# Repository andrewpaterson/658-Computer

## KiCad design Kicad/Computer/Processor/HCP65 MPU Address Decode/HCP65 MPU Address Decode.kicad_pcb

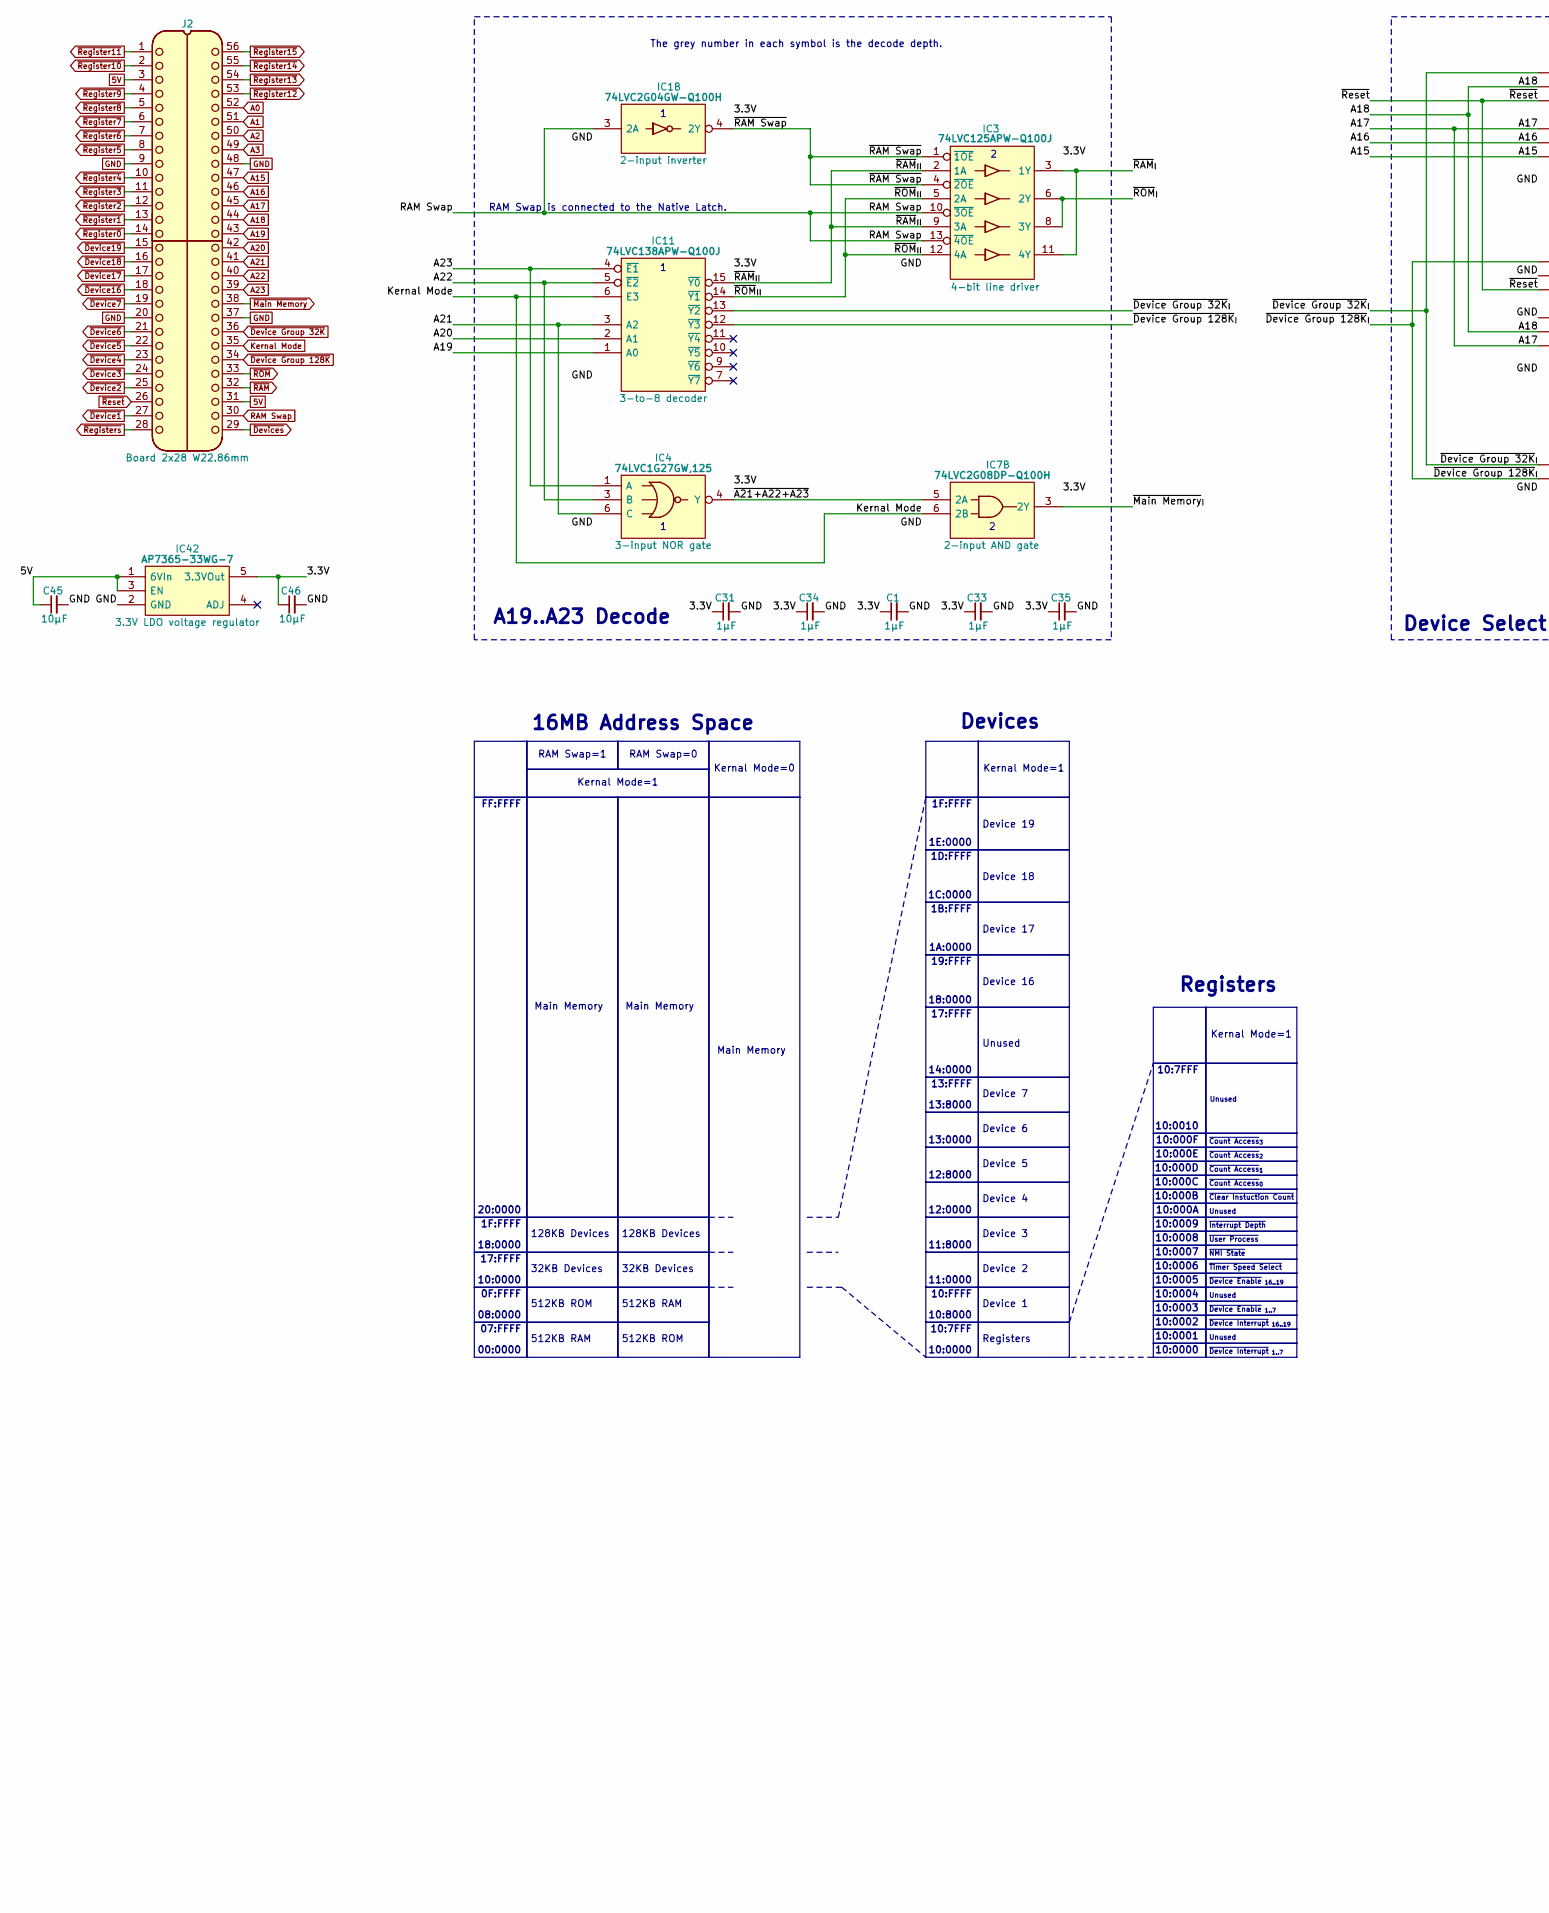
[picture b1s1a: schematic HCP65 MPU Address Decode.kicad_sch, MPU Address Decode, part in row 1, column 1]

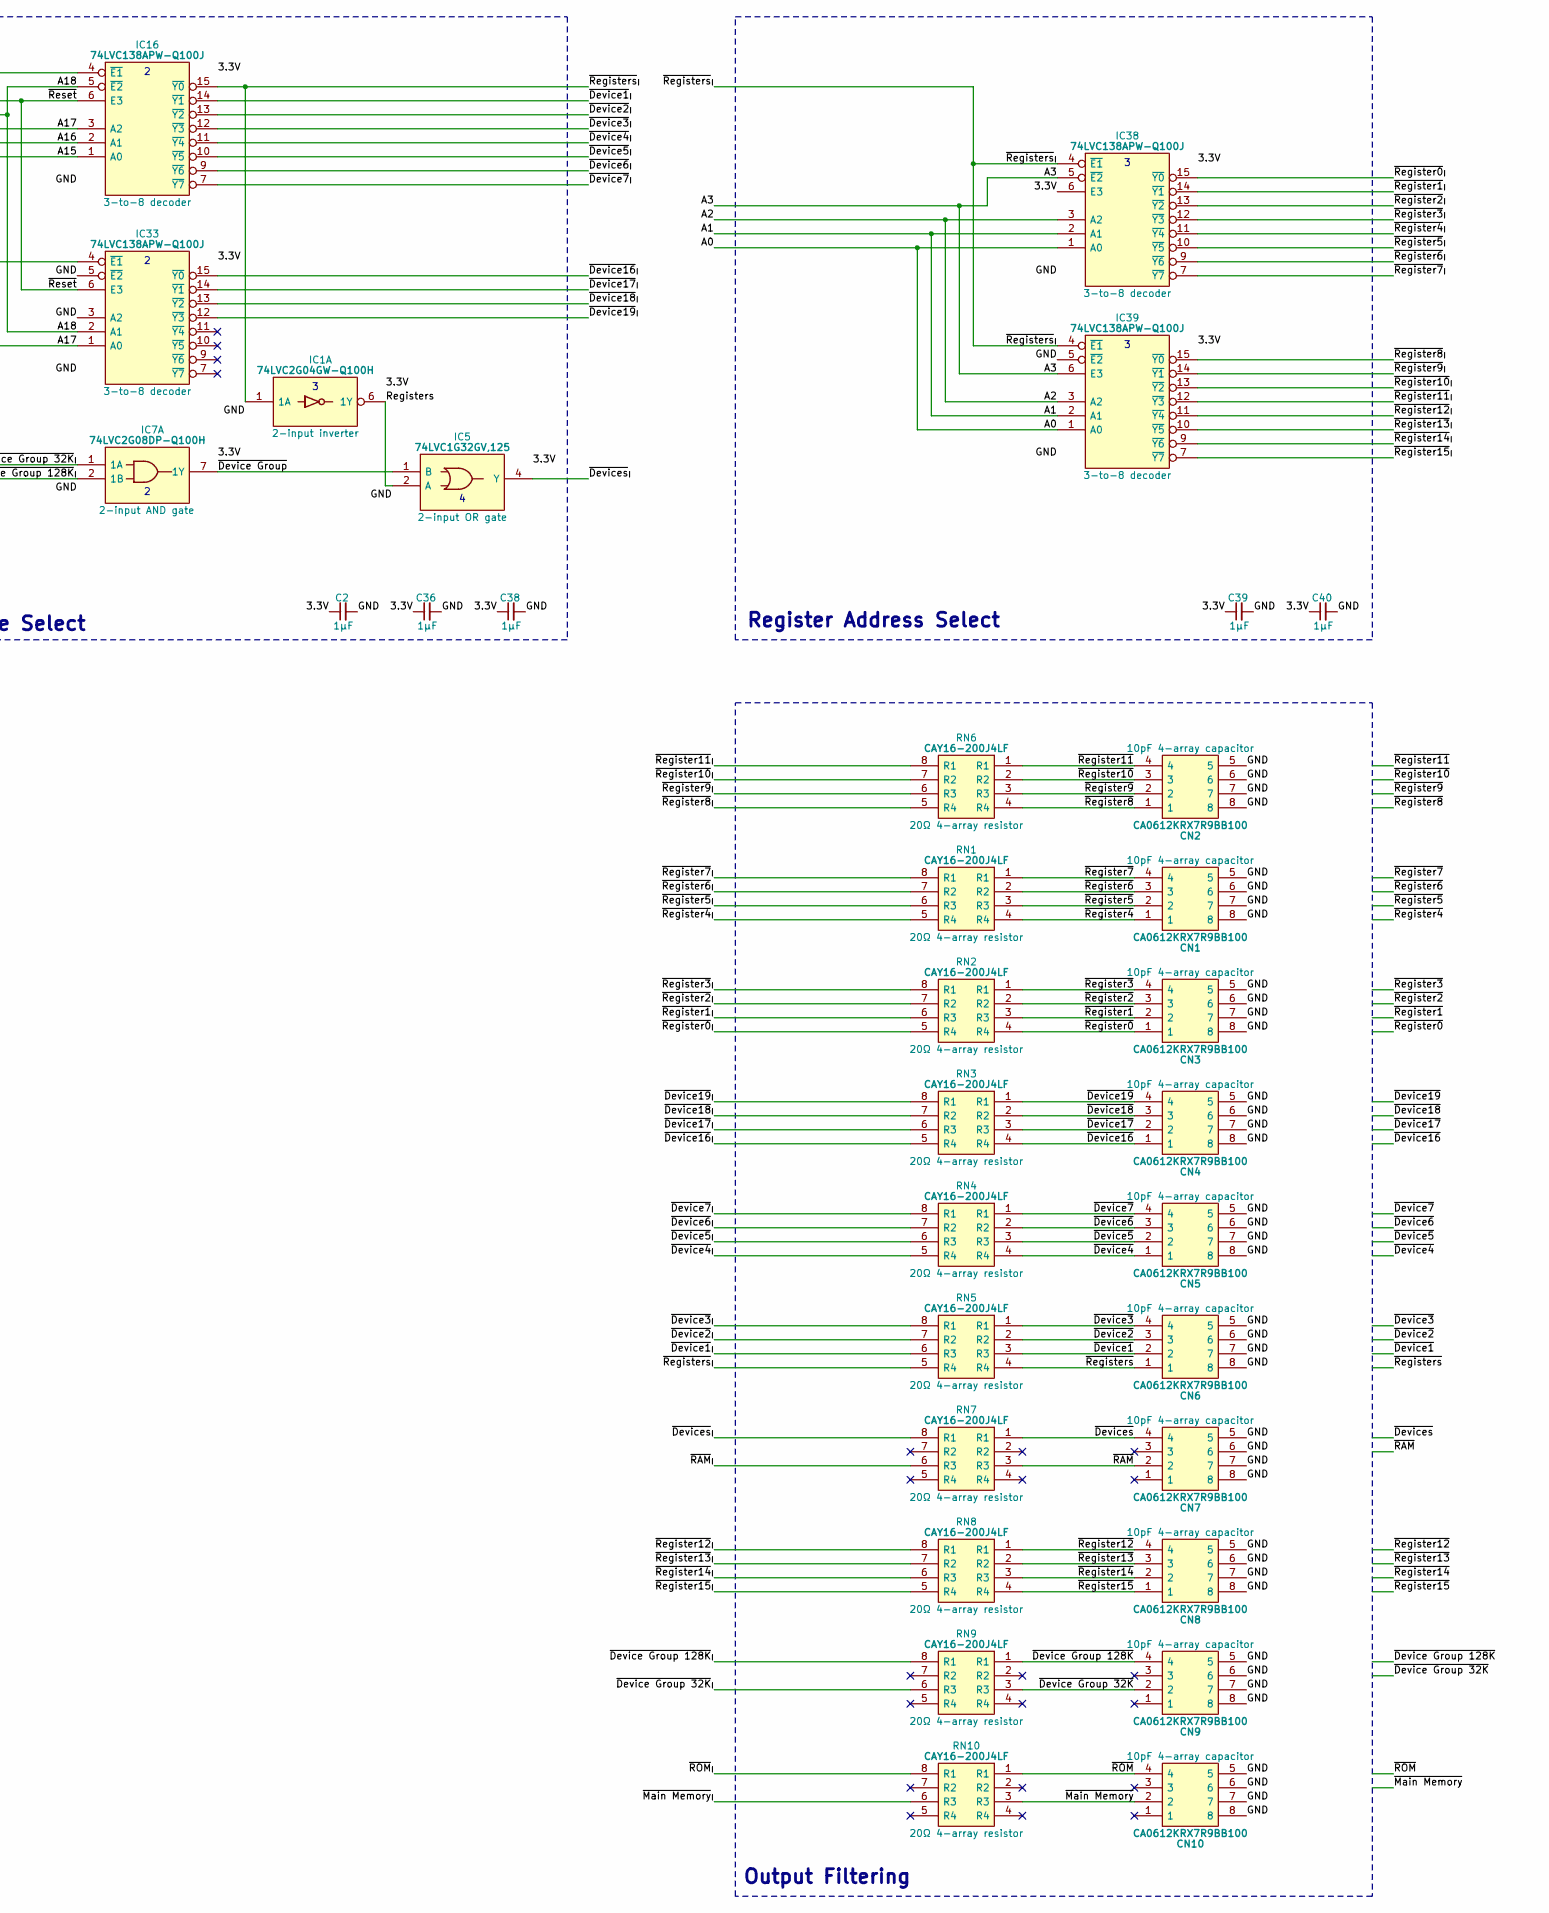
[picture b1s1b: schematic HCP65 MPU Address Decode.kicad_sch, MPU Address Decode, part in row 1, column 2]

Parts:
C1, C2, C31, C33, C34, C35, C36, C38, C39, C40: 1μF; C_0805
C45, C46: 10μF; C_0805
CN1, CN2, CN3, CN4, CN5, CN6, CN7, CN8, CN9, CN10: CA0612KRX7R9BB100; Manufacturer_Part_Number CA0612KRX7R9BB102; Mouser Part Number 603-CA612KRX7R9BB102
IC1: 74LVC2G04GW-Q100H; SOP65P210X110-6N; Manufacturer_Part_Number 74LVC2G04GW-Q100H; Mouser Part Number 771-74LVC2G04GWQ100H
IC3: 74LVC125APW-Q100J; SOP65P640X110-14N; Manufacturer_Part_Number 74LVC125APW-Q100J; Mouser Part Number 771-74LVC125APWQ100J
IC4: 74LVC1G27GW,125; SOP65P210X110-6N; Mouser Part Number 771-74LVC1G27GW125
IC5: 74LVC1G32GV,125; SOT95P275X110-5N; Manufacturer_Part_Number 74LVC1G32GV,125; Mouser Part Number 771-LVC1G32GV125
IC7: 74LVC2G08DP-Q100H; SOP65P400X110-8N; Manufacturer_Part_Number 74LVC2G08DP-Q100H; Mouser Part Number 771-74LVC2G08DPQ100H
IC11, IC16, IC33, IC38, IC39: 74LVC138APW-Q100J; SOP65P640X110-16N; Mouser Part Number 771-74LVC138APWQ100J
IC42: AP7365-33WG-7; SOT95P285X130-5N; Manufacturer_Part_Number AP7365-33WG-7; Mouser Part Number 621-AP7365-33WG-7
J2: Board 2x28 W22.86mm; DIP-56_Board_W22.86mm
RN1, RN2, RN3, RN4, RN5, RN6, RN7, RN8, RN9, RN10: CAY16-200J4LF; CAY16-F4; Manufacturer_Part_Number CAY16-331J4LF; Mouser Part Number 652-CAY16-331J4LF

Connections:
5V: C45.1, IC42.1 (6VIn), IC42.3 (EN), J2.3, J2.31
/3.3V: C1.1, C2.1, C31.1, C33.1, C34.1, C35.1, C36.1, C38.1, C39.1, C40.1, C46.1, IC1.5 (3V), IC3.14 (3V), IC4.5 (3V), IC5.5 (3V), IC7.8 (3V), IC11.16 (3V), IC16.16 (3V), IC33.16 (3V), IC38.6 (E3), IC38.16 (3V), IC39.16 (3V), IC42.5 (3.3VOut)
/Registers: IC1.6 (1Y), IC5.2 (A)
/~A21+A22+A23: IC4.4 (Y), IC7.5 (2A)
/~Device1_{I}: IC16.14 (~Y1), RN5.6 (R3)
/~Device2_{I}: IC16.13 (~Y2), RN5.7 (R2)
/~Device3_{I}: IC16.12 (~Y3), RN5.8 (R1)
/~Device4_{I}: IC16.11 (~Y4), RN4.5 (R4)
/~Device5_{I}: IC16.10 (~Y5), RN4.6 (R3)
/~Device6_{I}: IC16.9 (~Y6), RN4.7 (R2)
/~Device7_{I}: IC16.7 (~Y7), RN4.8 (R1)
/~Device16_{I}: IC33.15 (~Y0), RN3.5 (R4)
/~Device17_{I}: IC33.14 (~Y1), RN3.6 (R3)
/~Device18_{I}: IC33.13 (~Y2), RN3.7 (R2)
/~Device19_{I}: IC33.12 (~Y3), RN3.8 (R1)
/~Device Group 32K_{I}: IC7.1 (1A), IC11.13 (~Y2), IC16.4 (~E1), RN9.6 (R3)
/~Device Group 128K_{I}: IC7.2 (1B), IC11.12 (~Y3), IC33.4 (~E1), RN9.8 (R1)
/~Device Group: IC5.1 (B), IC7.7 (1Y)
/~Devices_{I}: IC5.4 (Y), RN7.8 (R1)
/~Main Memory_{I}: IC7.3 (2Y), RN10.6 (R3)
/~RAM Swap: IC1.4 (2Y), IC3.1 (~1OE), IC3.4 (~2OE)
/~RAM_{II}: IC3.2 (1A), IC3.9 (3A), IC11.15 (~Y0)
/~RAM_{I}: IC3.3 (1Y), IC3.11 (4Y), RN7.6 (R3)
/~ROM_{II}: IC3.5 (2A), IC3.12 (4A), IC11.14 (~Y1)
/~ROM_{I}: IC3.6 (2Y), IC3.8 (3Y), RN10.8 (R1)
/~Register0_{I}: IC38.15 (~Y0), RN2.5 (R4)
/~Register1_{I}: IC38.14 (~Y1), RN2.6 (R3)
/~Register2_{I}: IC38.13 (~Y2), RN2.7 (R2)
/~Register3_{I}: IC38.12 (~Y3), RN2.8 (R1)
/~Register4_{I}: IC38.11 (~Y4), RN1.5 (R4)
/~Register5_{I}: IC38.10 (~Y5), RN1.6 (R3)
/~Register6_{I}: IC38.9 (~Y6), RN1.7 (R2)
/~Register7_{I}: IC38.7 (~Y7), RN1.8 (R1)
/~Register8_{I}: IC39.15 (~Y0), RN6.5 (R4)
/~Register9_{I}: IC39.14 (~Y1), RN6.6 (R3)
/~Register10_{I}: IC39.13 (~Y2), RN6.7 (R2)
/~Register11_{I}: IC39.12 (~Y3), RN6.8 (R1)
/~Register12_{I}: IC39.11 (~Y4), RN8.8 (R1)
/~Register13_{I}: IC39.10 (~Y5), RN8.7 (R2)
/~Register14_{I}: IC39.9 (~Y6), RN8.6 (R3)
/~Register15_{I}: IC39.7 (~Y7), RN8.5 (R4)
/~Registers_{I}: IC1.1 (1A), IC16.15 (~Y0), IC38.4 (~E1), IC39.4 (~E1), RN5.5 (R4)
A0: IC38.1 (A0), IC39.1 (A0), J2.52
A1: IC38.2 (A1), IC39.2 (A1), J2.51
A2: IC38.3 (A2), IC39.3 (A2), J2.50
A3: IC38.5 (~E2), IC39.6 (E3), J2.49
A15: IC16.1 (A0), J2.47
A16: IC16.2 (A1), J2.46
A17: IC16.3 (A2), IC33.1 (A0), J2.45
A18: IC16.5 (~E2), IC33.2 (A1), J2.44
A19: IC11.1 (A0), J2.43
A20: IC11.2 (A1), J2.42
A21: IC4.6 (C), IC11.3 (A2), J2.41
A22: IC4.3 (B), IC11.5 (~E2), J2.40
A23: IC4.1 (A), IC11.4 (~E1), J2.39
GND: C1.2, C2.2, C31.2, C33.2, C34.2, C35.2, C36.2, C38.2, C39.2, C40.2, C45.2, C46.2, CN1.5, CN1.6, CN1.7, CN1.8, CN2.5, CN2.6, CN2.7, CN2.8, CN3.5, CN3.6, CN3.7, CN3.8, CN4.5, CN4.6, CN4.7, CN4.8, CN5.5, CN5.6, CN5.7, CN5.8, CN6.5, CN6.6, CN6.7, CN6.8, CN7.5, CN7.6, CN7.7, CN7.8, CN8.5, CN8.6, CN8.7, CN8.8, CN9.5, CN9.6, CN9.7, CN9.8, CN10.5, CN10.6, CN10.7, CN10.8, IC1.2 (GND), IC3.7 (GND), IC4.2 (GND), IC5.3 (GND), IC7.4 (GND), IC11.8 (GND), IC16.8 (GND), IC33.3 (A2), IC33.5 (~E2), IC33.8 (GND), IC38.8 (GND), IC39.5 (~E2), IC39.8 (GND), IC42.2 (GND), J2.9, J2.20, J2.37, J2.48
Kernal Mode: IC7.6 (2B), IC11.6 (E3), J2.35
RAM Swap: IC1.3 (2A), IC3.10 (~3OE), IC3.13 (~4OE), J2.30
~Device1: CN6.2, J2.27, RN5.3 (R3)
~Device2: CN6.3, J2.25, RN5.2 (R2)
~Device3: CN6.4, J2.24, RN5.1 (R1)
~Device4: CN5.1, J2.23, RN4.4 (R4)
~Device5: CN5.2, J2.22, RN4.3 (R3)
~Device6: CN5.3, J2.21, RN4.2 (R2)
~Device7: CN5.4, J2.19, RN4.1 (R1)
~Device16: CN4.1, J2.18, RN3.4 (R4)
~Device17: CN4.2, J2.17, RN3.3 (R3)
~Device18: CN4.3, J2.16, RN3.2 (R2)
~Device19: CN4.4, J2.15, RN3.1 (R1)
~Device Group 32K: CN9.2, J2.36, RN9.3 (R3)
~Device Group 128K: CN9.4, J2.34, RN9.1 (R1)
~Devices: CN7.4, J2.29, RN7.1 (R1)
~Main Memory: CN10.2, J2.38, RN10.3 (R3)
~RAM: CN7.2, J2.32, RN7.3 (R3)
~ROM: CN10.4, J2.33, RN10.1 (R1)
~Register0: CN3.1, J2.14, RN2.4 (R4)
~Register1: CN3.2, J2.13, RN2.3 (R3)
~Register2: CN3.3, J2.12, RN2.2 (R2)
~Register3: CN3.4, J2.11, RN2.1 (R1)
~Register4: CN1.1, J2.10, RN1.4 (R4)
~Register5: CN1.2, J2.8, RN1.3 (R3)
~Register6: CN1.3, J2.7, RN1.2 (R2)
~Register7: CN1.4, J2.6, RN1.1 (R1)
~Register8: CN2.1, J2.5, RN6.4 (R4)
~Register9: CN2.2, J2.4, RN6.3 (R3)
~Register10: CN2.3, J2.2, RN6.2 (R2)
~Register11: CN2.4, J2.1, RN6.1 (R1)
~Register12: CN8.4, J2.53, RN8.1 (R1)
~Register13: CN8.3, J2.54, RN8.2 (R2)
~Register14: CN8.2, J2.55, RN8.3 (R3)
~Register15: CN8.1, J2.56, RN8.4 (R4)
~Registers: CN6.1, J2.28, RN5.4 (R4)
~Reset: IC16.6 (E3), IC33.6 (E3), J2.26

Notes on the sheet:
17:FFFF
10:0009
Unused
512KB RAM
18:0000
RAM Swap=1
14:0000
10:0006
13:0000
1E:0000
Main Memory
~{Timer Speed Select}
10:8000
10:000F
Kernal Mode=1
Device 17
Kernal Mode=0
~{Interrupt Depth}
~{Device Enable}_{ 1..7}
1C:0000
10:0001
00:0000
19:FFFF
13:FFFF
~{Device Enable}_{ 16..19}
10:0004
10:0000
10:7FFF
10:FFFF
10:000A
~{Device Interrupt}_{ 16..19}
20:0000
11:0000
~{User Process}
Device 5
128KB Devices
512KB ROM
1B:FFFF
Device 6
Registers

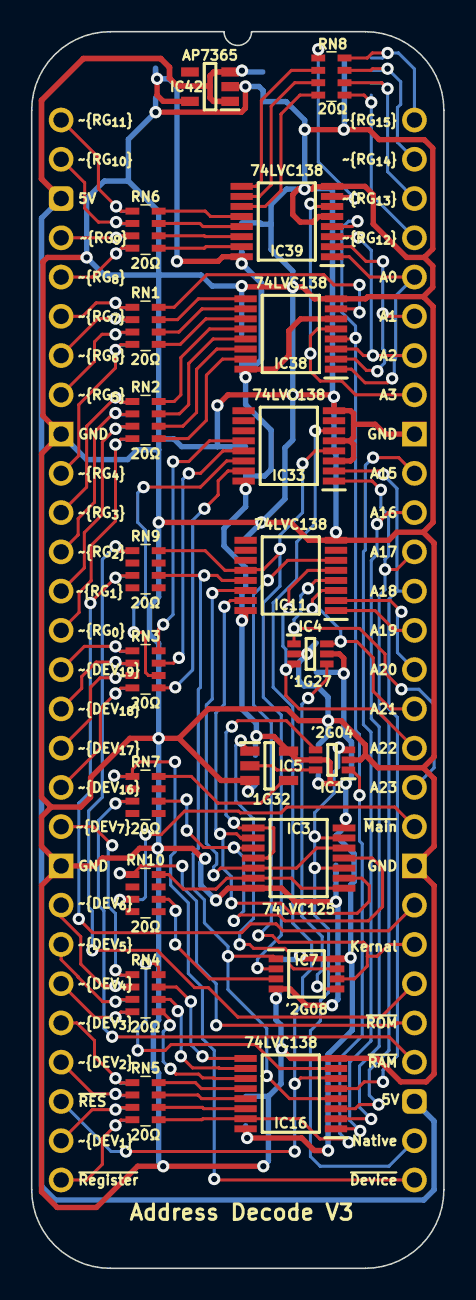
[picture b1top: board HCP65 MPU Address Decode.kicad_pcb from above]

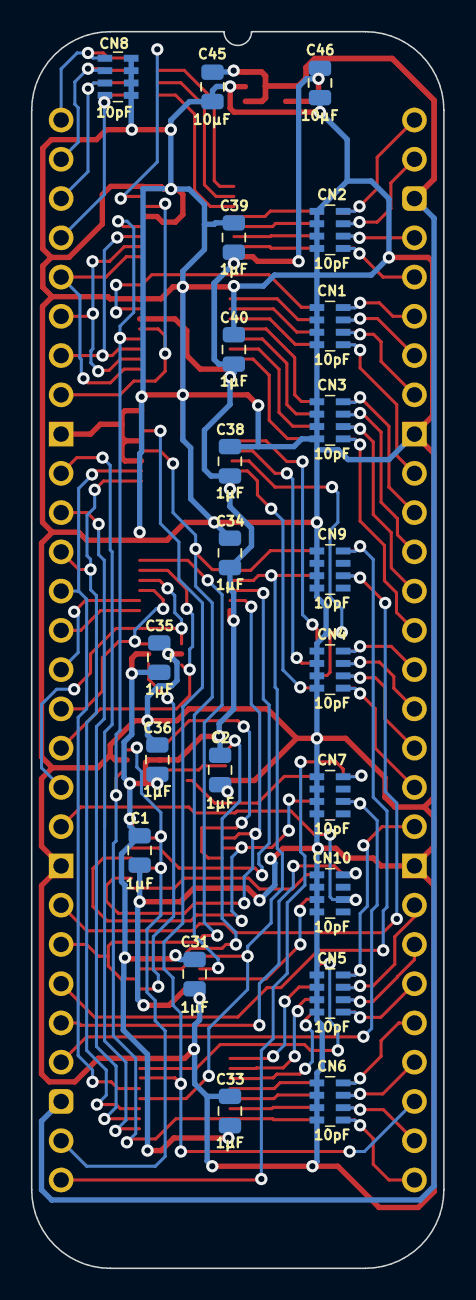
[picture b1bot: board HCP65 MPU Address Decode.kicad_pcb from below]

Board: 2 copper layers, 26.7 x 80.0 mm, 44 parts (22 on the bottom side), 93 nets.

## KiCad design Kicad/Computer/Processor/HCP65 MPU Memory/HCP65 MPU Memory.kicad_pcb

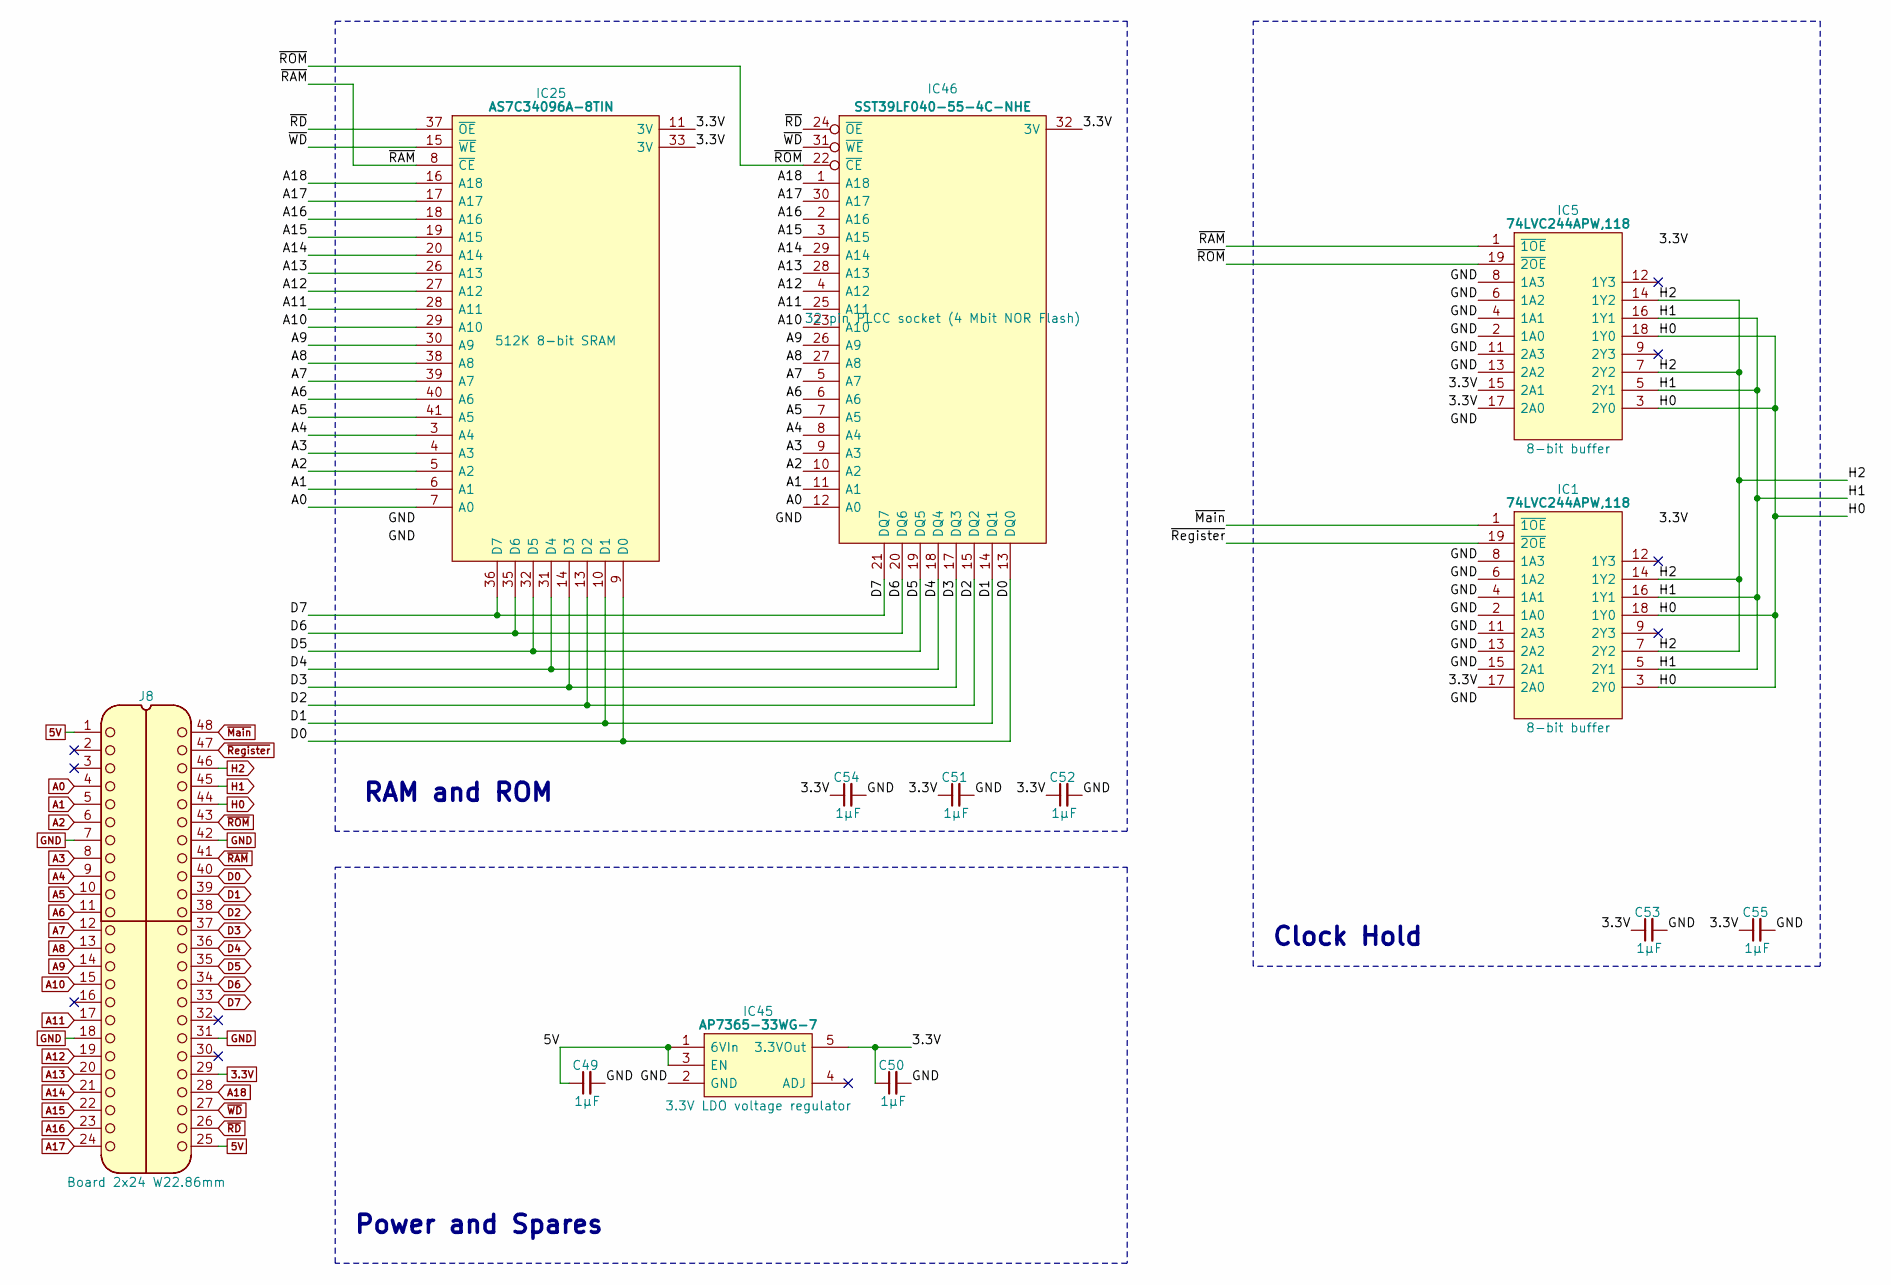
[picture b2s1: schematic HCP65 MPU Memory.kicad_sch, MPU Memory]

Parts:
C49, C50, C51, C52, C53, C54, C55: 1μF; C_0805
IC1, IC5: 74LVC244APW,118; SOP65P640X110-20N; Manufacturer_Part_Number 74LVC244APW,118; Mouser Part Number 771-74LVC244APW-T
IC25: AS7C34096A-8TIN; SOP80P1176X120-44N; Manufacturer_Part_Number AS7C34096A-8TIN; Mouser Part Number 913-AS7C34096A-8TIN
IC45: AP7365-33WG-7; SOT95P285X130-5N; Manufacturer_Part_Number AP7365-33WG-7; Mouser Part Number 621-AP7365-33WG-7
IC46: SST39LF040-55-4C-NHE; 5408803224008; Manufacturer_Part_Number SST39LF040-55-4C-NHE
J8: Board 2x24 W22.86mm; DIP-48_Board_W22.86mm

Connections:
3.3V: C50.1, C51.1, C52.1, C53.1, C54.1, C55.1, IC1.17 (2A0), IC1.20 (3V), IC5.15 (2A1), IC5.17 (2A0), IC5.20 (3V), IC25.11 (3V), IC25.33 (3V), IC45.5 (3.3VOut), IC46.32 (3V), J8.29
5V: C49.1, IC45.1 (6VIn), IC45.3 (EN), J8.1, J8.25
A0: IC25.7 (A0), IC46.12 (A0), J8.4
A1: IC25.6 (A1), IC46.11 (A1), J8.5
A2: IC25.5 (A2), IC46.10 (A2), J8.6
A3: IC25.4 (A3), IC46.9 (A3), J8.8
A4: IC25.3 (A4), IC46.8 (A4), J8.9
A5: IC25.41 (A5), IC46.7 (A5), J8.10
A6: IC25.40 (A6), IC46.6 (A6), J8.11
A7: IC25.39 (A7), IC46.5 (A7), J8.12
A8: IC25.38 (A8), IC46.27 (A8), J8.13
A9: IC25.30 (A9), IC46.26 (A9), J8.14
A10: IC25.29 (A10), IC46.23 (A10), J8.15
A11: IC25.28 (A11), IC46.25 (A11), J8.17
A12: IC25.27 (A12), IC46.4 (A12), J8.19
A13: IC25.26 (A13), IC46.28 (A13), J8.20
A14: IC25.20 (A14), IC46.29 (A14), J8.21
A15: IC25.19 (A15), IC46.3 (A15), J8.22
A16: IC25.18 (A16), IC46.2 (A16), J8.23
A17: IC25.17 (A17), IC46.30 (A17), J8.24
A18: IC25.16 (A18), IC46.1 (A18), J8.28
D0: IC25.9 (D0), IC46.13 (DQ0), J8.40
D1: IC25.10 (D1), IC46.14 (DQ1), J8.39
D2: IC25.13 (D2), IC46.15 (DQ2), J8.38
D3: IC25.14 (D3), IC46.17 (DQ3), J8.37
D4: IC25.31 (D4), IC46.18 (DQ4), J8.36
D5: IC25.32 (D5), IC46.19 (DQ5), J8.35
D6: IC25.35 (D6), IC46.20 (DQ6), J8.34
D7: IC25.36 (D7), IC46.21 (DQ7), J8.33
GND: C49.2, C50.2, C51.2, C52.2, C53.2, C54.2, C55.2, IC1.2 (1A0), IC1.4 (1A1), IC1.6 (1A2), IC1.8 (1A3), IC1.10 (GND), IC1.11 (2A3), IC1.13 (2A2), IC1.15 (2A1), IC5.2 (1A0), IC5.4 (1A1), IC5.6 (1A2), IC5.8 (1A3), IC5.10 (GND), IC5.11 (2A3), IC5.13 (2A2), IC25.12 (GND), IC25.34 (GND), IC45.2 (GND), IC46.16 (GND), J8.7, J8.18, J8.31, J8.42
H0: IC1.3 (2Y0), IC1.18 (1Y0), IC5.3 (2Y0), IC5.18 (1Y0), J8.44
H1: IC1.5 (2Y1), IC1.16 (1Y1), IC5.5 (2Y1), IC5.16 (1Y1), J8.45
H2: IC1.7 (2Y2), IC1.14 (1Y2), IC5.7 (2Y2), IC5.14 (1Y2), J8.46
~Main: IC1.1 (~1OE), J8.48
~RAM: IC5.1 (~1OE), IC25.8 (~CE), J8.41
~RD: IC25.37 (~OE), IC46.24 (~OE), J8.26
~ROM: IC5.19 (~2OE), IC46.22 (~CE), J8.43
~Register: IC1.19 (~2OE), J8.47
~WD: IC25.15 (~WE), IC46.31 (~WE), J8.27

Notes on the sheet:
Power and Spares
Clock Hold
RAM and ROM

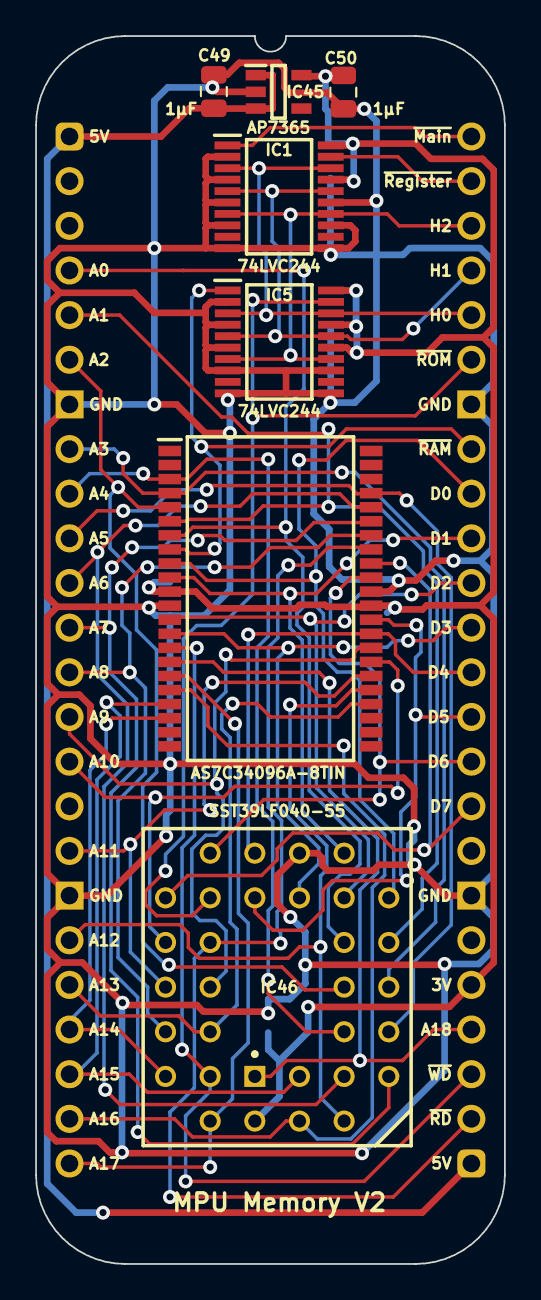
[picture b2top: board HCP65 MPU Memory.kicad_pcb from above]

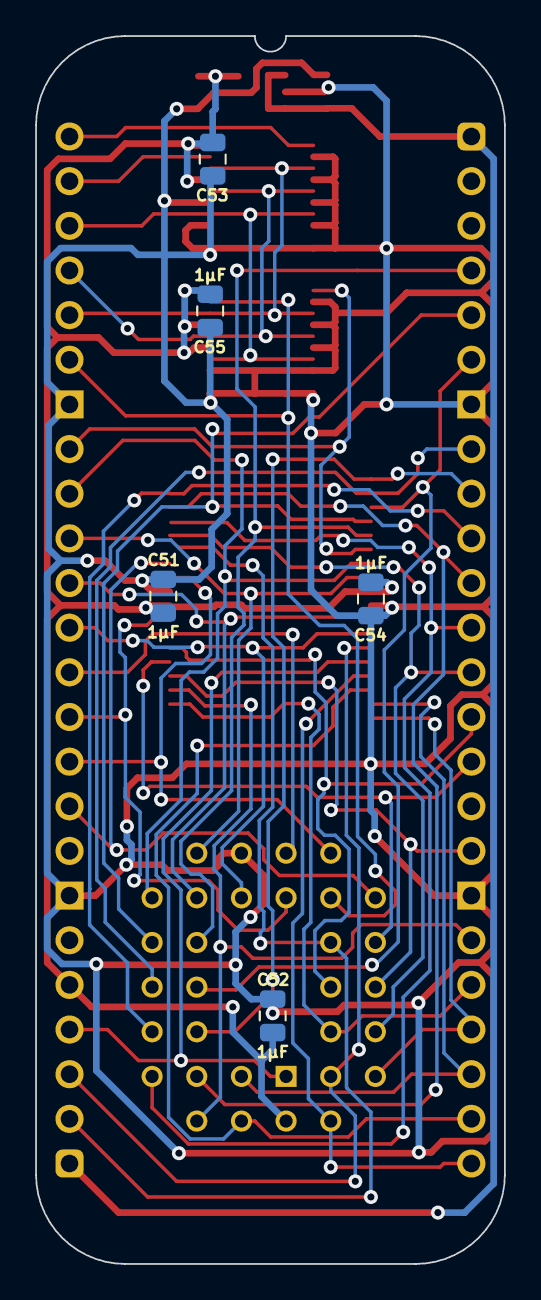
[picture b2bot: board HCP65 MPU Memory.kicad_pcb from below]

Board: 2 copper layers, 26.7 x 69.9 mm, 13 parts (5 on the bottom side), 39 nets.

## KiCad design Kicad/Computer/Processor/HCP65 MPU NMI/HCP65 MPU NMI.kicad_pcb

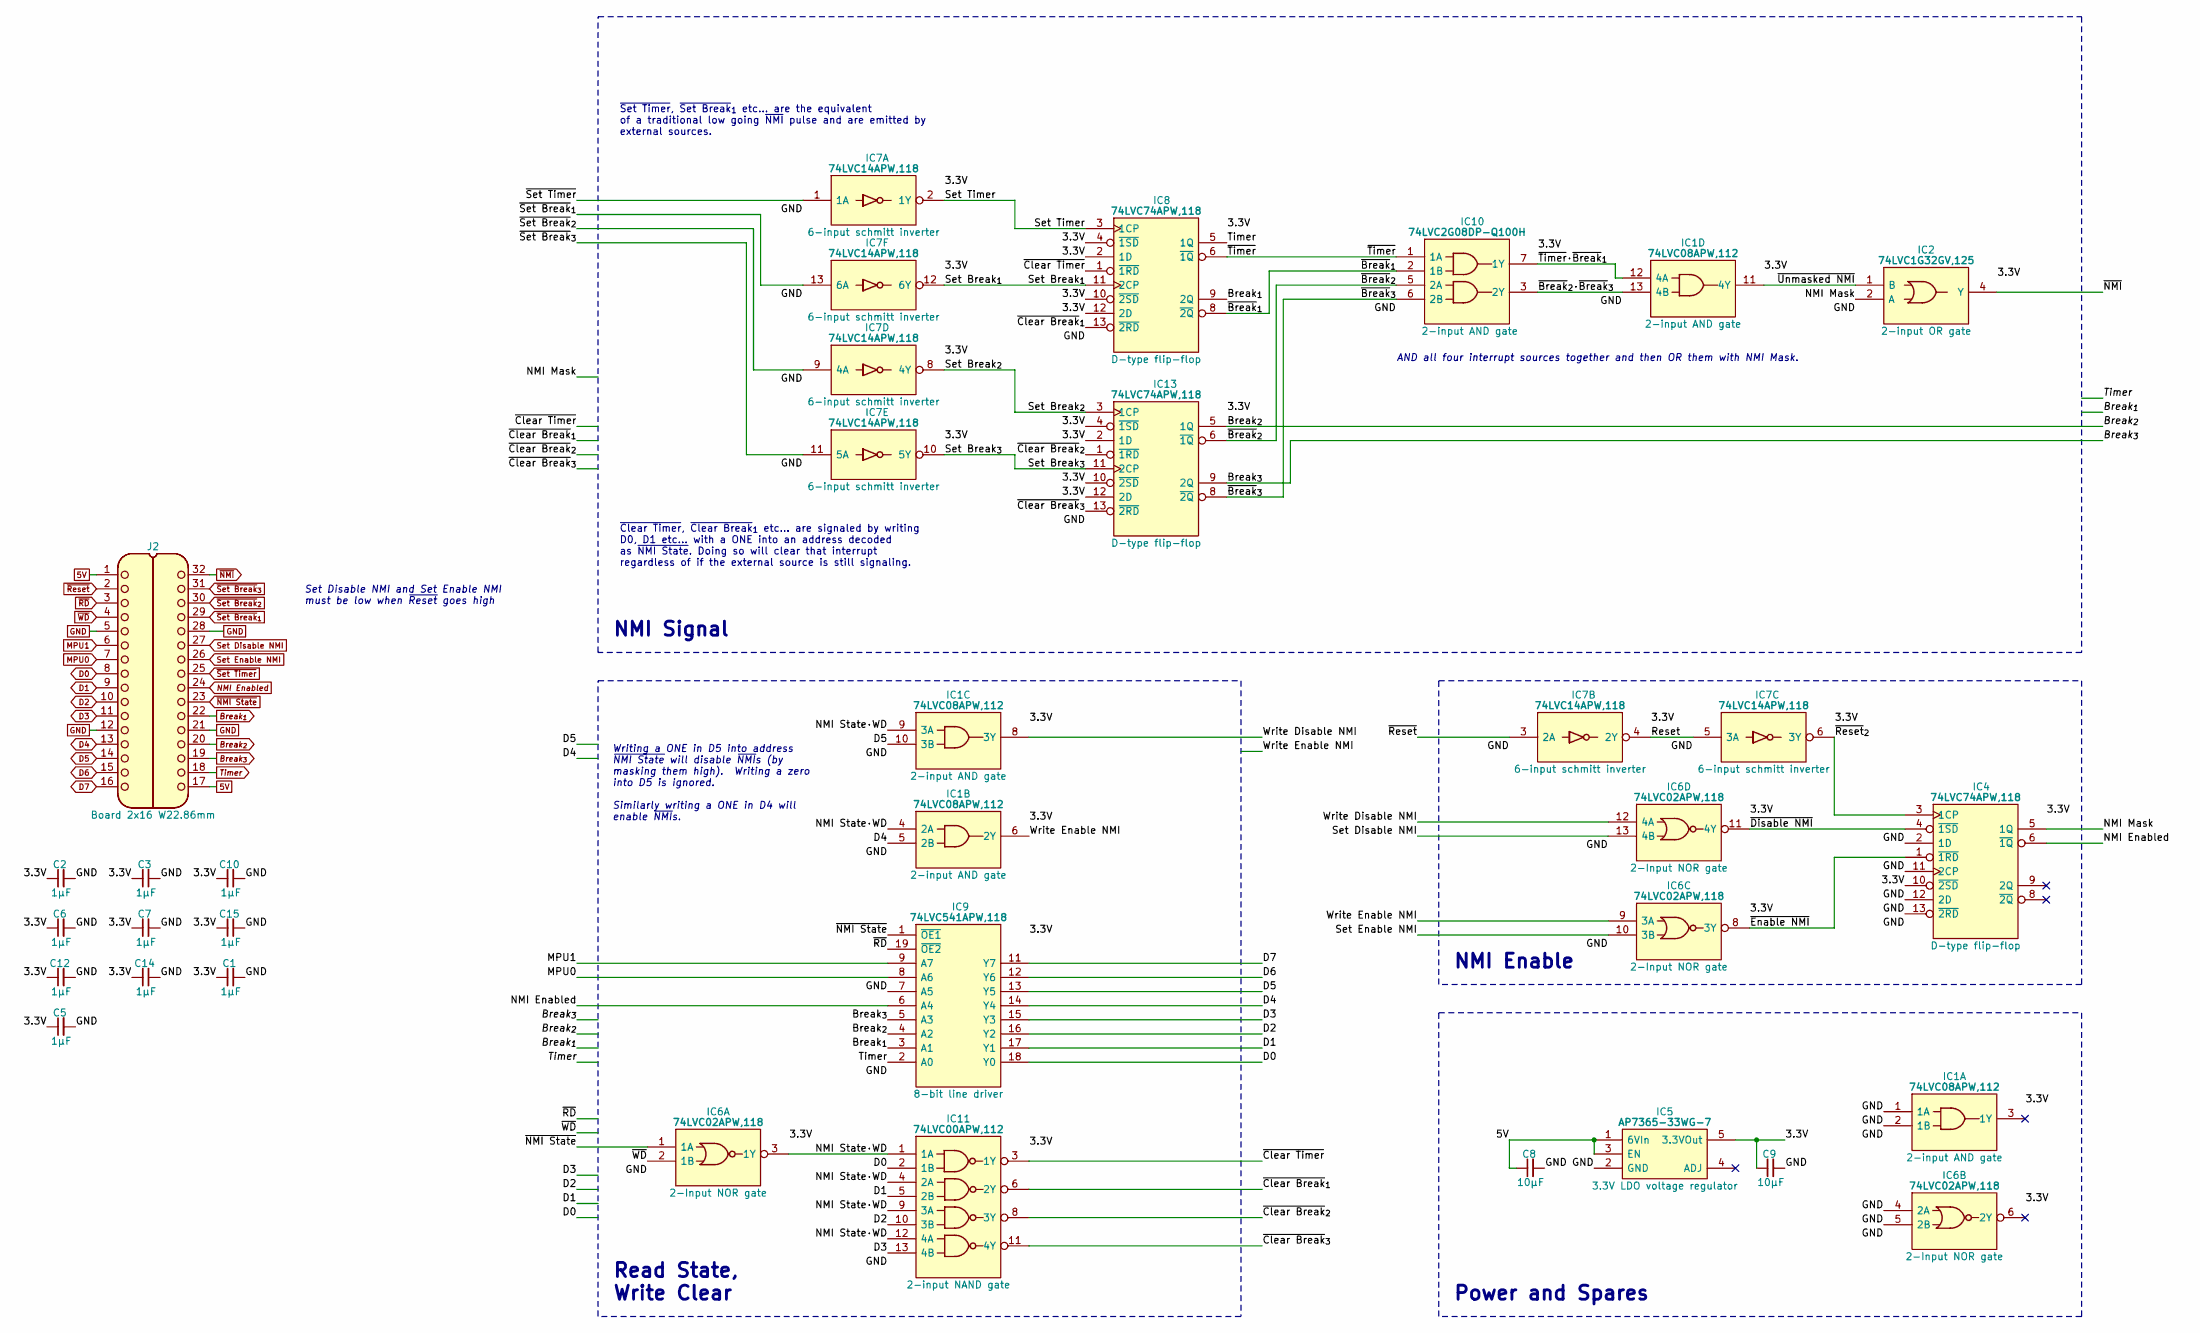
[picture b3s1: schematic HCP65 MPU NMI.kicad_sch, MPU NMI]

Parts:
C1, C2, C3, C5, C6, C7, C10, C12, C14, C15: 1μF; C_0805
C8, C9: 10μF; C_0805
IC1: 74LVC08APW,112; SOP65P640X110-14N; Manufacturer_Part_Number 74LVC08APW,112; Mouser Part Number 771-74LVC08APW
IC2: 74LVC1G32GV,125; SOT95P275X110-5N; Manufacturer_Part_Number 74LVC1G32GV,125; Mouser Part Number 771-LVC1G32GV125
IC4, IC8, IC13: 74LVC74APW,118; SOP65P640X110-14N; Mouser Part Number 771-74LVC74APW-T
IC5: AP7365-33WG-7; SOT95P285X130-5N; Manufacturer_Part_Number AP7365-33WG-7; Mouser Part Number 621-AP7365-33WG-7
IC6: 74LVC02APW,118; SOP65P640X110-14N; Mouser Part Number 771-74LVC02APW-T
IC7: 74LVC14APW,118; SOP65P640X110-14N; Manufacturer_Part_Number 74LVC14APW,118; Mouser Part Number 771-74LVC14APW-T
IC9: 74LVC541APW,118; SOP65P640X110-20N; Mouser Part Number 771-74LVC541APW-T
IC10: 74LVC2G08DP-Q100H; SOP65P400X110-8N; Manufacturer_Part_Number 74LVC2G08DP-Q100H; Mouser Part Number 771-74LVC2G08DPQ100H
IC11: 74LVC00APW,112; SOP65P640X110-14N; Mouser Part Number 771-74LVC00APW
J2: Board 2x16 W22.86mm; DIP-32_Board_W22.86mm

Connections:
5V: C8.1, IC5.1 (6VIn), IC5.3 (EN), J2.1, J2.17
/NMI Mask: IC2.2 (A), IC4.5 (1Q)
/NMI State·WD: IC1.4 (2A), IC1.9 (3A), IC6.3 (1Y), IC11.1 (1A), IC11.4 (2A), IC11.9 (3A), IC11.12 (4A)
/Reset: IC7.4 (2Y), IC7.5 (3A)
/Set Break_{1}: IC7.12 (6Y), IC8.11 (2CP)
/Set Break_{2}: IC7.8 (4Y), IC13.3 (1CP)
/Set Break_{3}: IC7.10 (5Y), IC13.11 (2CP)
/Set Timer: IC7.2 (1Y), IC8.3 (1CP)
/Timer: IC8.5 (1Q), IC9.2 (A0)
/Write Disable NMI: IC1.8 (3Y), IC6.12 (4A)
/Write Enable NMI: IC1.6 (2Y), IC6.9 (3A)
/~Break_{1}: IC8.8 (~2Q), IC10.2 (1B)
/~Break_{2}: IC10.5 (2A), IC13.6 (~1Q)
/~Break_{2}·~Break_{3}: IC1.13 (4B), IC10.3 (2Y)
/~Break_{3}: IC10.6 (2B), IC13.8 (~2Q)
/~Clear Break_{1}: IC8.13 (~2RD), IC11.6 (2Y)
/~Clear Break_{2}: IC11.8 (3Y), IC13.1 (~1RD)
/~Clear Break_{3}: IC11.11 (4Y), IC13.13 (~2RD)
/~Clear Timer: IC8.1 (~1RD), IC11.3 (1Y)
/~Disable NMI: IC4.4 (~1SD), IC6.11 (4Y)
/~Enable NMI: IC4.1 (~1RD), IC6.8 (3Y)
/~Reset_{2}: IC4.3 (1CP), IC7.6 (3Y)
/~Timer: IC8.6 (~1Q), IC10.1 (1A)
/~Timer·~Break_{1}: IC1.12 (4A), IC10.7 (1Y)
/~Unmasked NMI: IC1.11 (4Y), IC2.1 (B)
Break_{1}: IC8.9 (2Q), IC9.3 (A1), J2.22
Break_{2}: IC9.4 (A2), IC13.5 (1Q), J2.20
Break_{3}: IC9.5 (A3), IC13.9 (2Q), J2.19
D0: IC9.18 (Y0), IC11.2 (1B), J2.8
D1: IC9.17 (Y1), IC11.5 (2B), J2.9
D2: IC9.16 (Y2), IC11.10 (3B), J2.10
D3: IC9.15 (Y3), IC11.13 (4B), J2.11
D4: IC1.5 (2B), IC9.14 (Y4), J2.13
D5: IC1.10 (3B), IC9.13 (Y5), J2.14
D6: IC9.12 (Y6), J2.15
D7: IC9.11 (Y7), J2.16
GND: C1.2, C2.2, C3.2, C5.2, C6.2, C7.2, C8.2, C9.2, C10.2, C12.2, C14.2, C15.2, IC1.1 (1A), IC1.2 (1B), IC1.7 (GND), IC2.3 (GND), IC4.2 (1D), IC4.7 (GND), IC4.11 (2CP), IC4.12 (2D), IC4.13 (~2RD), IC5.2 (GND), IC6.4 (2A), IC6.5 (2B), IC6.7 (GND), IC7.7 (GND), IC8.7 (GND), IC9.7 (A5), IC9.10 (GND), IC10.4 (GND), IC11.7 (GND), IC13.7 (GND), J2.5, J2.12, J2.21, J2.28
MPU0: IC9.8 (A6), J2.7
MPU1: IC9.9 (A7), J2.6
NMI Enabled: IC4.6 (~1Q), IC9.6 (A4), J2.24
Set Disable NMI: IC6.13 (4B), J2.27
Set Enable NMI: IC6.10 (3B), J2.26
~NMI State: IC6.1 (1A), IC9.1 (~OE1), J2.23
~NMI: IC2.4 (Y), J2.32
~RD: IC9.19 (~OE2), J2.3
~Reset: IC7.3 (2A), J2.2
~Set Break_{1}: IC7.13 (6A), J2.29
~Set Break_{2}: IC7.9 (4A), J2.30
~Set Break_{3}: IC7.11 (5A), J2.31
~Set Timer: IC7.1 (1A), J2.25
~WD: IC6.2 (1B), J2.4

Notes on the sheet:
AND all four interrupt sources together and then OR them with NMI Mask.
NMI Enable
Set Disable NMI and Set Enable NMI must be low when ~{Reset} goes high
Read State, Write Clear
Writing a ONE in D5 into address ~{NMI State} will disable ~{NMI}s (by masking them high). Writing a zero into D5 is ignored. Similarly writing a ONE in D4 will enable ~{NMI}s.
NMI Signal
Power and Spares
~{Set Timer}, ~{Set Break}_{1} etc... are the equivalent of a traditional low going ~{NMI} pulse and are emitted by external sources.
~{Clear Timer}, ~{Clear Break}_{1} etc... are signaled by writing D0, D1 etc... with a ONE into an address decoded as ~{NMI State}. Doing so will clear that interrupt regardless of if the external source is still signaling.

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
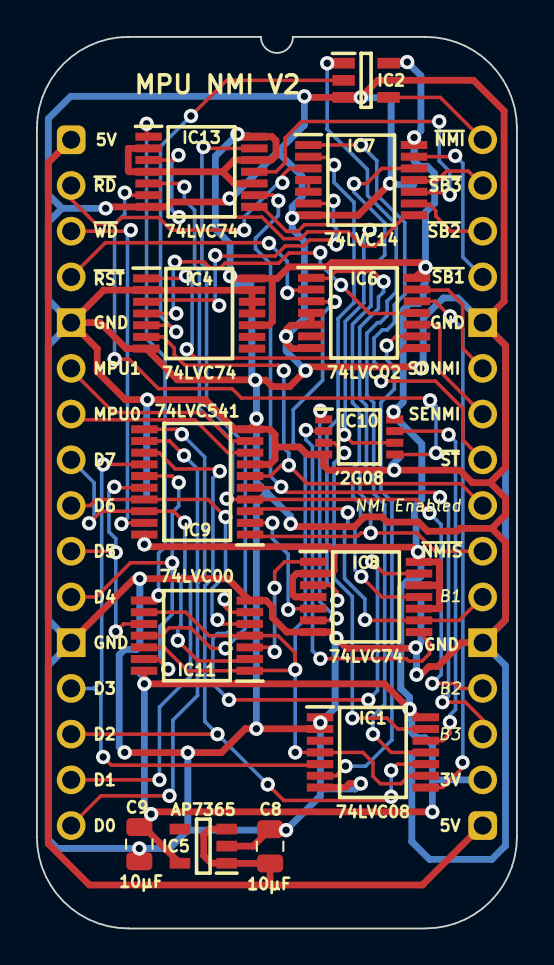
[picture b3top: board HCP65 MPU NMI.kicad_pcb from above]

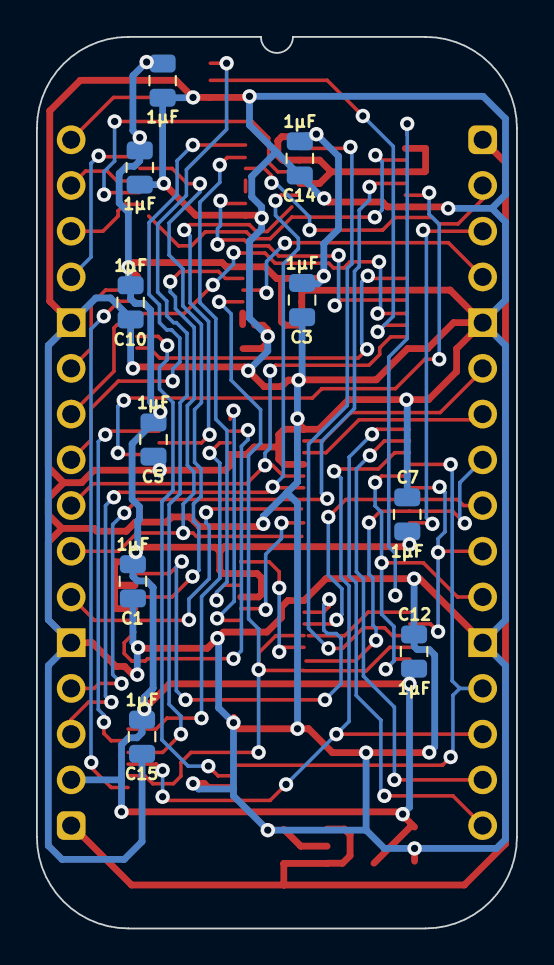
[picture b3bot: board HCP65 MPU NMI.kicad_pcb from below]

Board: 2 copper layers, 26.7 x 49.5 mm, 24 parts (10 on the bottom side), 52 nets.
